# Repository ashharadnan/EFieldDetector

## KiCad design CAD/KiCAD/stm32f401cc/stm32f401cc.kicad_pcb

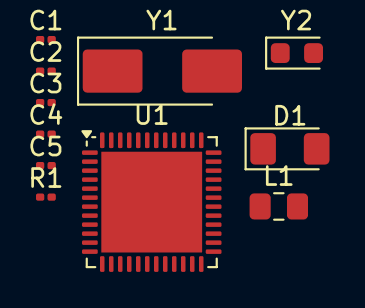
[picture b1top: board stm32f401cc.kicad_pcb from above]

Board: 2 copper layers, 11 parts (0 on the bottom side), 10 nets, no tracks yet.

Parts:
C1, C2, C3, C4, C5: C_Small; C_0201_0603Metric
D1: LED_BLUE; LED_1206_3216Metric_Pad1.42x1.75mm_HandSolder
L1: L_Iron_Small; C_0805_2012Metric_Pad1.18x1.45mm_HandSolder
R1: 15; R_0201_0603Metric
U1: STM32F401CCUx; QFN-48-1EP_7x7mm_P0.5mm_EP5.6x5.6mm
Y1: 25MHz; Crystal_SMD_Abracon_ABM3-2Pin_5.0x3.2mm_HandSoldering
Y2: 32.768kHz; Crystal_SMD_2012-2Pin_2.0x1.2mm_HandSoldering

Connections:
+3.3V: D1.2 (A), L1.1, U1.24 (VDD), U1.36 (VDD), U1.48 (VDD)
GND: C1.1, C2.1, C3.1, C4.1, C5.1, U1.8 (VSSA), U1.23 (VSS), U1.35 (VSS), U1.47 (VSS), U1.49 (VSS)
unnamed: D1.1 (K), R1.1
unnamed: R1.2, U1.2 (PC13)
unnamed: C2.2, U1.3 (PC14), Y2.2
unnamed: C1.2, U1.4 (PC15), Y2.1
unnamed: C3.2, U1.5 (PH0), Y1.2
unnamed: C4.2, U1.6 (PH1), Y1.1
unnamed: C5.2, U1.22 (VCAP1)
unnamed: L1.2, U1.9 (VREF+)

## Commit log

2025-05-08 Init
2025-05-08 Initialise
2025-05-08 Startup fix
2025-05-09 ADS1115 working
2025-05-09 Project v0.1
    Screen working
    ADC working in differential mode
    Vpkpk displayed (Recalculated every 100ms)
2025-05-09 Project v0.1
    Screen working
    ADC working in differential mode \pm 1024
    Vpkpk displayed (Recalculated every 100ms)
2025-05-22 KiCAD
2025-05-27 acquire
2025-05-27 check diff mode acquire
2025-07-02 common-mode
2025-07-02 common-mode + time sample filter
